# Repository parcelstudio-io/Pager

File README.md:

# Mochi Pager

Mochi Pager is a pager-sized, expressive voice AI companion. The first product target is a rounded handheld device with two large round eyes, curious idle gaze, a sliding live caption, microphone, speaker, Wi-Fi, BLE, and optional standalone 4G LTE—and exactly two physical controls: the top conversation button and a power slide switch. The conversation button deliberately opens or closes a visibly live session; while it is open, the user and assistant can speak in a full-duplex, voice-interruptible conversation without pressing for each turn, while the assistant's words slide through the caption below its face. A companion mobile app onboards the device over BLE (Wi-Fi credentials, cellular APN, account claiming) and shows an encrypted local cache of opt-in cloud conversation history. The pager connects through a private gateway to the OpenAI Realtime API; it does not run the language model on the device.

The current phase is V1 interaction implementation plus EVT (engineering validation) planning. A zero-dependency local session broker and browser device simulator now provide the first runnable full-duplex slice; embedded firmware, the mobile app, cloud history, and cellular work remain staged behind it.

## Start here

- [Product concept](docs/design/0001_mochi_pager_product_concept.md)
- [V1 prototype high-level design](docs/prototype/0001_v1_high_level_design.md)
- [V1 beginner build guide and exact materials](docs/prototype/0002_v1_beginner_build_guide.md)
- [Companion app and synchronization architecture](docs/design/0002_companion_app_and_sync_architecture.md)
- [Carrier board hardware design](docs/design/0003_mochi_carrier_board_design.md)
- [MVP requirements](docs/requirements/0001_mvp_requirements.md)
- [Component sources and staged BOM](docs/research/0001_component_sources_and_bom.md)
- [Shared-conversation and video source audit](docs/research/0002_reference_observations.md)
- [Independent verification and corrections](docs/research/0003_independent_verification_and_corrections.md)
- [35-project-day build plan plus companion-app track](scrum/20260830/task_0001/daily_plan.md)
- [Technical decision log](docs/decisions/README.md)
- [Beginner IoT and electrical-engineering course](edu/README.md)

## Current verdict

The interaction mule is already ordered: one full M5Stack CoreS3 K128, recorded in the [daily log](scrum/20260830/task_0001/daily_log.md). Confirm only a known-good data-capable USB-C cable now; do not buy a second CoreS3. First run the laptop V1-A slice, then use the K128's documented full-duplex audio path to measure simultaneous capture/playback, AEC feasibility, voice barge-in, on-device captions, and truthful session indication. Use Wi-Fi and then a phone hotspot before adding radio complexity. Buy the separate SIM7600G-H cellular mule only after the Wi-Fi full-duplex vertical slice passes its gate. Do not buy a final battery, custom display, bare cellular module, or 5G hardware yet.

This ordering protects the project from three expensive early mistakes: choosing an enclosure before measuring the parts, choosing a battery before measuring modem peaks, and integrating RF onto the first PCB.

The major load-bearing claims reviewed in the 2026-08-30/31 verification pass, its corrections, and its explicitly unverifiable items are logged in [research 0003](docs/research/0003_independent_verification_and_corrections.md). That pass also added requirements the first draft missed: the sliding caption, companion app, and two-control constraint.

## Run V1-A now

Node.js 20 or newer and an OpenAI API project are required. The standard API key stays in the local server process.

```bash
cp .env.example .env
# Edit .env and replace OPENAI_API_KEY=replace_me
npm test
npm start
```

Then open `http://localhost:3000`. No `npm install` is required because V1-A has no runtime package dependencies. The idle face begins calm and centered: its first curious gesture arrives after 3–5 seconds, later gestures follow 6–12 second pauses, and every synchronized up/down glance, side-to-side look-around, or clockwise/counterclockwise roll returns to center. Each gesture now uses brief saccades separated by still fixations instead of continuous pupil drift; the cream eye aperture follows vertical gaze like an eyelid opening, while speaking no longer produces a rhythmic eye bob. Conversation and battery state take priority. Face animation loads as an optional enhancement after Start/Stop is wired, so an animation import or initialization failure leaves a static face without disabling conversation control. The gateway renders the versioned [`prompt/mochi-realtime.ftl`](prompt/mochi-realtime.ftl) on the server, so the browser cannot inject history or system instructions. The localhost default has no real account/history service and truthfully marks that context unavailable. API use may incur charges; set a conservative project budget before testing. The [beginner build guide](docs/prototype/0002_v1_beginner_build_guide.md) contains the complete safety, setup, acceptance, and CoreS3 bring-up sequence.

## Repository organization

```text
docs/
  decisions/       numbered architecture decision records (ADRs)
  design/          product and industrial-design specifications
  requirements/    measurable product requirements
  research/        source audits, comparisons, and BOMs
edu/               progressive IoT and electrical-engineering course for software engineers
prompt/            version-controlled server-side Realtime instruction templates
scrum/
  YYYYMMDD/
    task_NNNN/      task brief, daily plan, evidence, and retrospective
hardware/           future PCB and mechanical source files
src/                production device, gateway, companion-app, and cloud code only
tests/              automated tests spanning production components
tools/              simulators, fixtures, flashing, and developer utilities
```

Create directories only when they gain real content. When implementation begins, a sensible source split is `src/device/`, `src/gateway/`, `src/app/` (the companion mobile app), and `src/cloud/`. Hardware design should live in `hardware/pcb/` and `hardware/mechanical/`, not under `src/`.

Task IDs are repository-wide, zero-padded, and monotonically increasing. Decision records have their own monotonically increasing sequence because a decision's history is independent of sprint/task history. Never renumber an accepted or superseded record.

## Reference boundary

The shared ChatGPT post exposes only one answer, which proposes a **95 × 60 × 30 mm** enclosure. The earlier conversation is not present in the public page, so this repository treats that size as a maximum envelope rather than inventing unavailable prior decisions.

The visual reference is Huy Vector's [Tiny Pocket AI Assistant](https://www.youtube.com/watch?v=25RGnr407PM) and its [build guide](https://www.huyvector.org/robots-kinetic/pocket-ai-assistant). We borrow its face-first charm, blinking eyes, compact status text, and cheeky personality. We do not copy its exposed battery, conductive frame, cloud service, or electronics as a product architecture.

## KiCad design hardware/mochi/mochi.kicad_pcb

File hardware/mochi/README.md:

# Mochi R1 Walter carrier

This directory contains a deterministic **electrical reference and placement study** for
the pager-size Mochi companion. It is intentionally useful for architecture review,
firmware pin contracts, component purchasing, and mechanical experiments. It is **not a
fabrication release**.

The current baseline is a 60 × 82 × 1.2 mm four-layer carrier around the orderable
QuickSpot Walter LTE-M/Wi-Fi/BLE/GNSS SoM. The previously proposed MIKROE-6396 Click was
removed because its official product page now reports it unavailable. The design decision
and alternatives are recorded in [ADR 0013](../../docs/decisions/0013_use_walter_family_for_rev_a_evt.md).

## Files

- [`mochi.kicad_sch`](mochi.kicad_sch) — KiCad system-level schematic.
- [`mochi.kicad_pcb`](mochi.kicad_pcb) — four-layer outline and reviewed component
  placement; intentionally unrouted.
- [`doc/design_manifest.json`](doc/design_manifest.json) — machine-readable electrical,
  configuration, and release-boundary contract.
- [`doc/bom.csv`](doc/bom.csv) — proposed parts and DNP state.
- [`doc/connectivity.csv`](doc/connectivity.csv) — exact named-net endpoints.
- [`doc/pin_map.csv`](doc/pin_map.csv) — Walter/ESP32 GPIO assignment.
- [`doc/bringup_and_validation.md`](doc/bringup_and_validation.md) — physical proof plan.
- [`doc/research_matrix.md`](doc/research_matrix.md) — dated primary-source comparison.
- [`reports/`](reports/) — KiCad/MCP and command-line check evidence.

The generated `Mochi_Reference.pretty` footprints are review geometry, except that the
Walter header pitch, pin order, pad centers, and antenna keepout follow QuickSpot's open
footprint. Every footprint must still be replaced or independently checked against the
exact ordered part and assembly process before fabrication.

## Reproduce the desk checks

From the repository root:

```bash
node tools/hardware/generate_mochi_reference.js
python3 tools/hardware/check_carrier_design.py
```

The current expected result is **66 passed, 2 warnings, 0 failed**. The warnings are
deliberate: the PCB has no routes, and the back-mounted Walter reference produces one
library-parity warning. KiCad ERC is zero. KiCad DRC otherwise reports the 168 expected
unconnected items and no unexpected physical-rule category.

KiCad MCP was also pointed at this exact project. Its full production quality gate is
expected to fail and is retained as useful evidence: a label-oriented system schematic
has zero explicit wires, the PCB is unrouted, and reference footprints are not a release
library. MCP did confirm clean ERC, 100% schematic-to-PCB named-pad transfer, matching
reference sets, a 60 × 82 mm frame, and zero courtyard issues.

## What the board connects

```text
USB-C charge only ─ protection ─ BQ25628E ─ SYS_ALWAYS ─ TPS22950 ─ SYS_SW ─ Walter VIN
                             │                    ▲                    └─ 200uF EVT reservoir
protected 1S pack + NTC ─────┘                    │
                                           latching slide

SYS_SW ─ TPS63802 ─ 3V3_PERIPH ─┬─ LCD + touch
                                ├─ MAX98357A ─ differential 8ohm speaker
                                ├─ TPS22918 ─ MIC_3V3 ─ PDM mic + isolation + cyan LED
                                └─ DNP TPS22918 ─ Arducam Mega + white LED
```

Walter contains the ESP32-S3, Wi-Fi/BLE, LTE-M/NB-IoT modem, nano-SIM, GNSS, RF front
end, and modem-to-ESP UART. The carrier therefore does not route a 50-ohm cellular trace,
SIM bus, 1.8 V modem GPIO, or user USB data.

## Stop conditions

Do not order a PCB from this directory until all of these are true:

- production symbols, footprints, land patterns, paste apertures, and exact order codes
  are frozen;
- the schematic is redrawn with conventional wires/hierarchy and peer-reviewed;
- the power stages are laid out from vendor reference layouts and the entire PCB is
  routed with zero unexplained ERC/DRC findings;
- enclosure CAD closes around the display, battery, speaker cavity, module, USB, switches,
  coax bends, and LTE antenna;
- a physical prototype passes the validation plan; and
- an RF/certification lab accepts the portable simultaneous-transmitter plan.

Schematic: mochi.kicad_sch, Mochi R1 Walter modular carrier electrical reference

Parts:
C1: 1uF 25V X7R; C1_C0603
C2: 10uF 25V X7R; C2_C0805
C3: 100nF 25V X7R; C3_C0402
C4: 47nF 25V X7R; C4_C0402
C5: 4.7uF 10V X7R; C5_C0603
C6: 10uF 10V X7R; C6_C0805
C7: 10uF 10V X7R; C7_C0805
C8: 10uF 10V X7R; C8_C0805
C9: 100nF 10V X7R; C9_C0402
C10: 1uF 10V X7R; C10_C0603
C11: 10uF 10V X7R; C11_C0805
C12: 10uF 10V X7R; C12_C0805
C13: 22uF 6.3V X7R; C13_C0805
C14: 100uF 6.3V low-ESR; C14_C1210
C15: 100uF 6.3V low-ESR; C15_C1210
C16: 10uF 10V X7R; C16_C0805
C17: 100nF 10V X7R; C17_C0402
C18: 1uF 6.3V X7R; C18_C0603
C19: 10uF 6.3V X7R; C19_C0805
C20: 100nF 6.3V X7R; C20_C0402
D1: CYAN CAPTURE LED; D1_LED0402
D2: AMBER BUTTON LED; D2_LED0402
D3: WHITE CAMERA POWER LED DNP; D3_LED0402; not fitted
D4: ESDA7P60-1U1M; D4_QFN-2
F1: 1206L075/24; F1_F1206
J1: USB4105-GF-A; J1_USB-C-16P
J2: Molex 5023520300; J2_DuraClik-3P-RA
J4: AS01808AO-SC18-WP-R; J4_Speaker-18x13-Spring
J5: WAVESHARE 1.69IN TOUCH LCD 27057; J5_GH1.25-12P-RA-VERIFY
J6: ARDUCAM MEGA 3MP B0400 DNP; J6_XH2.54-1x6-RA; not fitted
L1: 1uH XGL4020-102; L1_L4x4
L2: 0.47uH XFL4015-471; L2_L4x4
MK1: IM69D129F; MK1_MEMS-5-3.5x2.65-BOTTOM-PORT
R1: 5.1k 1%; R1_R0402
R2: 5.1k 1%; R2_R0402
R3: 4.99k 1%; R3_R0402
R4: 5.23k 1%; R4_R0402
R5: 30.1k 1%; R5_R0402
R6: 100k 1%; R6_R0402
R7: 523R 1%; R7_R0402
R8: 511k 1%; R8_R0402
R9: 91k 1%; R9_R0402
R10: 4.7k 1%; R10_R0402
R11: 4.7k 1%; R11_R0402
R12: 10k 1%; R12_R0402
R13: 1.5k 1%; R13_R0402
R14: 100k 1%; R14_R0402
R15: 1.5k 1%; R15_R0402
R16: 100k 1%; R16_R0402
R17: 100k 1% DNP; R17_R0402; not fitted
R18: 1.5k 1% DNP; R18_R0402; not fitted
RS1: 10m 1% Kelvin; RS1_R1206-Kelvin
SW1: LATCHING POWER SLIDE; SW1_Slide-SPST-RA-TBD
SW2: ILLUMINATED CONVERSATION BUTTON; SW2_Top-Button-TBD
TP1: DEBUG_TX; TP1_TestPoint-1mm
TP2: DEBUG_RX; TP2_TestPoint-1mm
TP3: WALTER_DFU_N; TP3_TestPoint-1mm
TP4: WALTER_RESET_N; TP4_TestPoint-1mm
TP5: MAIN_FAULT_N; TP5_TestPoint-1mm
TP6: 3V3_POWER_GOOD; TP6_TestPoint-1mm
TP7: BQ_INTERRUPT; TP7_TestPoint-1mm
TP8: GROUND; TP8_TestPoint-1mm
TP9: WALTER_3V3_OUT; TP9_TestPoint-1mm
TP10: GAUGE_ALERT; TP10_TestPoint-1mm
TP11: BQ_POWER_GOOD; TP11_TestPoint-1mm
U1: TPD2EUSB30; U1_SOT23-3
U3: BQ25628E; U3_WQFN-18-2.5x3
U4: MAX17055ETB+T; U4_TDFN-10-2x2.5
U5: TPS22950; U5_SOT23-6
U6: TPS63802; U6_VSON-10-3x2
U10: WALTER P000000100 N16R2; U10_WALTER-28-REF
U12: TPS22918; U12_SOT23-6
U13: SN74LVC2G125; U13_VSSOP-8
U14: MAX98357AETE+T; U14_TQFN-16-3x3
U15: TPS22918 DNP CAMERA; U15_SOT23-6; not fitted

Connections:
3V3_PERIPH: C13.1, C19.1, C20.1, J5.1 (VCC), R8.1, R10.2, R11.2, R12.2, U6.5 (VOUT), U12.1 (VIN), U14.1 (VDD), U15.1 (VIN)
3V3_PG_TP: TP6.1, U6.7 (PG)
AMBER_LED: D2.1 (A), U10.13 (IO2)
AMBER_LED_K: D2.2 (K), R13.1
AMP_SD: R16.1, U10.12 (IO42), U14.6 (SD_MODE)
BAT_NTC: J2.2 (NTC), R4.2, R5.1, U3.11 (TS)
BB_FB: R8.2, R9.1, U6.6 (FB)
BB_L1: L2.1, U6.3 (L1)
BB_L2: L2.2, U6.4 (L2)
BQ_BTST: C4.1, U3.4 (BTST)
BQ_INT_N_TP: TP7.1, U3.14 (INT_N)
BQ_PG_N_TP: TP11.1, U3.15 (PG_N)
BQ_PMID: C2.1, C3.1, U3.2 (PMID)
BQ_REGN: C5.1, U3.5 (REGN)
BQ_SW: C4.2, L1.1, U3.3 (SW)
BTN_CONV: R12.1, SW2.1 (SIGNAL), U10.10 (IO40)
CAM_3V3: D3.1 (A), J6.1 (VCC), U15.3 (VOUT)
CAM_CS: J6.6 (CS), U10.14 (IO1)
CAM_EN: R17.1, U10.21 (IO17), U15.2 (EN)
CAM_LED_K: D3.2 (K), R18.1
CAPTURE_EN: R14.1, U10.11 (IO41), U12.2 (EN)
CYAN_LED_K: D1.2 (K), R15.1
DBG_RX: TP2.1, U10.2 (IO44/RX0)
DBG_TX: TP1.1, U10.3 (IO43/TX0)
GAUGE_ALRT_N: TP10.1, U4.6 (ALRT_N)
GND: C1.2, C2.2, C3.2, C5.2, C6.2, C7.2, C8.2, C9.2, C10.2, C11.2, C12.2, C13.2, C14.2, C15.2, C16.2, C17.2, C18.2, C19.2, C20.2, D4.2 (A), J1.2 (GND), J1.5 (SHIELD), J5.2 (GND), J6.2 (GND), MK1.2 (GND), MK1.5 (L/R), R1.2, R2.2, R3.2, R5.2, R6.2, R7.2, R9.2, R13.2, R14.2, R15.2, R16.2, R17.2, R18.2, RS1.2 (SYSTEM), SW2.2 (GND), TP8.1, U1.3 (GND), U3.8 (GND), U3.16 (CE_N), U4.3 (CSN), U5.6 (GND), U6.8 (GND), U10.27 (GND), U12.4 (GND), U13.2 (GND), U13.3 (OE1_N), U13.6 (OE2_N), U14.2 (GND), U15.4 (GND)
I2C_SCL: J5.10 (TP_SCL), R11.1, U3.13 (SCL), U4.5 (SCL), U10.24 (IO9)
I2C_SDA: J5.9 (TP_SDA), R10.1, U3.12 (SDA), U4.4 (SDA), U10.23 (IO8)
I2S_BCLK: U10.17 (IO6), U14.3 (BCLK)
I2S_DOUT: U10.19 (IO15), U14.5 (DIN)
I2S_LRCLK: U10.18 (IO7), U14.4 (LRCLK)
LCD_BL: J5.8 (LCD_BL), U10.9 (IO39)
LCD_CS: J5.5 (LCD_CS), U10.25 (IO10)
LCD_DC: J5.6 (LCD_DC), U10.8 (IO38)
MAIN_FLT_N: TP5.1, U5.5 (FLT_N)
MAIN_ILIM: R7.1, U5.4 (ILIM)
MIC_3V3: C18.1, D1.1 (A), MK1.1 (VDD), U12.3 (VOUT), U13.1 (VCC)
PACK_N: J2.3 (PACK-), RS1.1 (PACK), U4.2 (CSP)
PACK_P: C8.1, C9.1, J2.1 (PACK+), U3.6 (BAT), U4.1 (BATT)
PDM_CLK_MCU: U10.15 (IO4), U13.4 (A1)
PDM_CLK_MIC: MK1.3 (CLK), U13.5 (Y1)
PDM_DATA_MCU: U10.16 (IO5), U13.8 (Y2)
PDM_DATA_MIC: MK1.4 (DATA), U13.7 (A2)
PWR_SW_ON: R6.1, SW1.2 (ON), U5.2 (ON)
SPI_MISO: J6.4 (MISO), U10.7 (IO13)
SPI_MOSI: J5.3 (LCD_DIN), J6.5 (MOSI), U10.6 (IO11)
SPI_SCK: J5.4 (LCD_CLK), J6.3 (SCK), U10.5 (IO12)
SPK_N: J4.2 (-), U14.8 (OUTN)
SPK_P: J4.1 (+), U14.7 (OUTP)
SYS_ALWAYS: C6.1, C7.1, C10.1, L1.2, SW1.1 (COMMON), U3.7 (SYS), U5.1 (VIN)
SYS_SW: C11.1, C12.1, C14.1, C15.1, C16.1, C17.1, U5.3 (VOUT), U6.1 (VIN), U6.2 (EN), U10.28 (VIN)
TOUCH_IRQ: J5.12 (TP_IRQ), U10.20 (IO16)
TS_BIAS: R4.1, U3.10 (TS_BIAS)
UI_RST_N: J5.7 (LCD_RST), J5.11 (TP_RST), U10.22 (IO18)
USB_CC1: J1.3 (CC1), R1.1, U1.1 (IO1)
USB_CC2: J1.4 (CC2), R2.1, U1.2 (IO2)
USB_ILIM_500MA: R3.1, U3.9 (ILIM)
VBUS_5V: C1.1, F1.2, U3.1 (VBUS)
VBUS_CONN: D4.1 (K), F1.1, J1.1 (VBUS)
WALTER_3V3_TP: TP9.1, U10.26 (3V3_OUT)
WALTER_DFU_N: TP3.1, U10.4 (IO0/DFU/3V3_EN)
WALTER_RESET_N: TP4.1, U10.1 (RESET/EN)

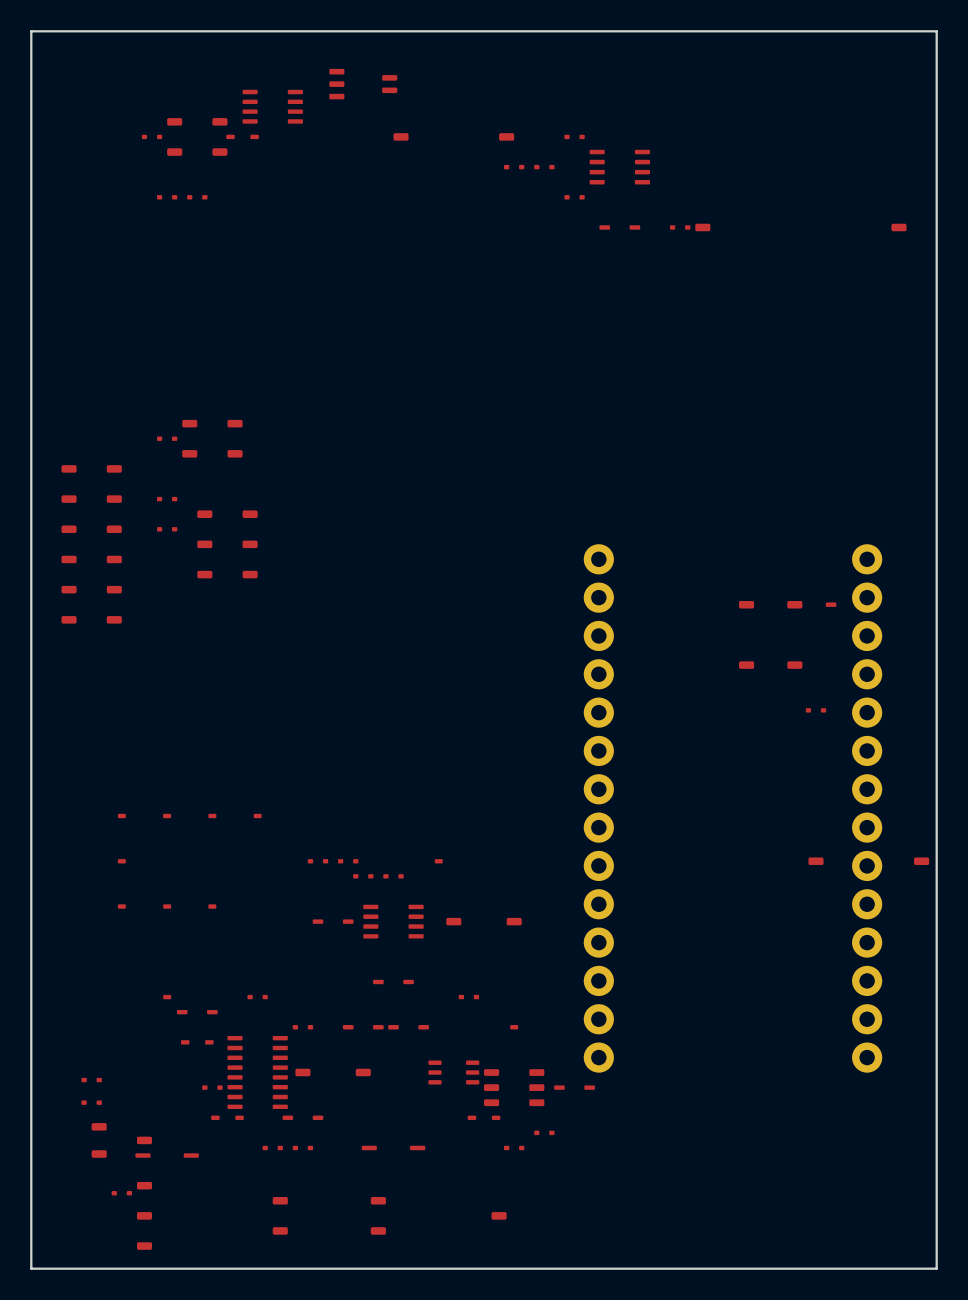
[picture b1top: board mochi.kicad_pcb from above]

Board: 4 copper layers, 60.0 x 82.0 mm, 75 parts (1 on the bottom side), 62 nets, no tracks yet.

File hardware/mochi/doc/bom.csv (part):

reference,value_or_mpn,manufacturer,role,population,datasheet,footprint_status
J1,USB4105-GF-A,GCT,User USB-C charge-only receptacle,FIT,https://gct.co/connector/usb4105,REFERENCE_ONLY_VERIFY_BEFORE_FAB
U1,TPD2EUSB30,Texas Instruments,USB-C CC1/CC2 ESD protection,FIT,https://www.ti.com/product/TPD2EUSB30,REFERENCE_ONLY_VERIFY_BEFORE_FAB
D4,ESDA7P60-1U1M,STMicroelectronics,USB VBUS TVS,FIT,https://www.st.com/en/protections-and-emi-filters/esda7p60-1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,REFERENCE_ONLY_VERIFY_BEFORE_FAB
F1,1206L075/24,Littelfuse,Resettable USB input fuse,FIT,https://www.littelfuse.com/products/polyswitch-resettable-pp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,REFERENCE_ONLY_VERIFY_BEFORE_FAB
R1,5.1k 1%,Generic,USB-C CC1 Rd,FIT,,REFERENCE_ONLY_VERIFY_BEFORE_FAB
R2,5.1k 1%,Generic,USB-C CC2 Rd,FIT,,REFERENCE_ONLY_VERIFY_BEFORE_FAB
U3,BQ25628E,Texas Instruments,1-cell 2A NVDC charger and power path,FIT,https://www.ti.com/lit/ds/symlink/bq25628e.pdf,REFERENCE_ONLY_VERIFY_BEFORE_FAB
L1,1uH XGL4020-102,Coilcraft,BQ25628E power-path inductor,FIT,https://www.coilcraft.com/en-us/products/power/shielded-indu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,REFERENCE_ONLY_VERIFY_BEFORE_FAB
C1,1uF 25V X7R,Generic,BQ VBUS bypass,FIT,,REFERENCE_ONLY_VERIFY_BEFORE_FAB
C2,10uF 25V X7R,Generic,BQ PMID bulk,FIT,,REFERENCE_ONLY_VERIFY_BEFORE_FAB
C3,100nF 25V X7R,Generic,BQ PMID high-frequency bypass,FIT,,REFERENCE_ONLY_VERIFY_BEFORE_FAB
C4,47nF 25V X7R,Generic,BQ bootstrap capacitor,FIT,,REFERENCE_ONLY_VERIFY_BEFORE_FAB
C5,4.7uF 10V X7R,Generic,BQ REGN bypass,FIT,,REFERENCE_ONLY_VERIFY_BEFORE_FAB
C6,10uF 10V X7R,Generic,BQ SYS bulk 1 of 2,FIT,,REFERENCE_ONLY_VERIFY_BEFORE_FAB
C7,10uF 10V X7R,Generic,BQ SYS bulk 2 of 2,FIT,,REFERENCE_ONLY_VERIFY_BEFORE_FAB
C8,10uF 10V X7R,Generic,BQ BAT bypass,FIT,,REFERENCE_ONLY_VERIFY_BEFORE_FAB
R3,4.99k 1%,Generic,"BQ input-current limit, about 500mA",FIT,https://www.ti.com/lit/ds/symlink/bq25628e.pdf,REFERENCE_ONLY_VERIFY_BEFORE_FAB
R4,5.23k 1%,Generic,BQ TS upper resistor for 103AT-class NTC,FIT,https://www.ti.com/lit/ds/symlink/bq25628e.pdf,REFERENCE_ONLY_VERIFY_BEFORE_FAB
R5,30.1k 1%,Generic,BQ TS lower resistor for 103AT-class NTC,FIT,https://www.ti.com/lit/ds/symlink/bq25628e.pdf,REFERENCE_ONLY_VERIFY_BEFORE_FAB
J2,Molex 5023520300,Molex,Protected pack connector,FIT,https://www.molex.com/en-us/products/part-detail/5023520300,REFERENCE_ONLY_VERIFY_BEFORE_FAB
RS1,10m 1% Kelvin,Vishay or equivalent,Fuel-gauge low-side shunt,FIT,,REFERENCE_ONLY_VERIFY_BEFORE_FAB
U4,MAX17055ETB+T,Analog Devices,Fuel gauge with current and time estimation,FIT,https://www.analog.com/en/products/MAX17055.html,REFERENCE_ONLY_VERIFY_BEFORE_FAB
C9,100nF 10V X7R,Generic,Fuel-gauge bypass,FIT,,REFERENCE_ONLY_VERIFY_BEFORE_FAB
SW1,LATCHING POWER SLIDE,C&K or Alps TBD,Only latching hardware power control,FIT,,REFERENCE_ONLY_VERIFY_BEFORE_FAB
R6,100k 1%,Generic,Power-enable fail-safe pull-down,FIT,,REFERENCE_ONLY_VERIFY_BEFORE_FAB
U5,TPS22950,Texas Instruments,Reverse-blocking adjustable-current-limit master load switch,FIT,https://www.ti.com/lit/ds/symlink/tps22950.pdf,REFERENCE_ONLY_VERIFY_BEFORE_FAB
R7,523R 1%,Generic,TPS22950 nominal about 2.4A current limit,FIT,https://www.ti.com/lit/ds/symlink/tps22950.pdf,REFERENCE_ONLY_VERIFY_BEFORE_FAB
C10,1uF 10V X7R,Generic,Master-switch input bypass,FIT,,REFERENCE_ONLY_VERIFY_BEFORE_FAB
C11,10uF 10V X7R,Generic,Master-switch output bulk,FIT,,REFERENCE_ONLY_VERIFY_BEFORE_FAB
U6,TPS63802,Texas Instruments,2A 3.3V peripheral buck-boost,FIT,https://www.ti.com/lit/ds/symlink/tps63802.pdf,REFERENCE_ONLY_VERIFY_BEFORE_FAB
L2,0.47uH XFL4015-471,Coilcraft,TPS63802 buck-boost inductor,FIT,https://www.coilcraft.com/en-us/products/power/shielded-indu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,REFERENCE_ONLY_VERIFY_BEFORE_FAB
R8,511k 1%,Generic,TPS63802 3.3V feedback upper,FIT,,REFERENCE_ONLY_VERIFY_BEFORE_FAB
R9,91k 1%,Generic,TPS63802 3.3V feedback lower,FIT,,REFERENCE_ONLY_VERIFY_BEFORE_FAB
C12,10uF 10V X7R,Generic,TPS63802 input bulk,FIT,,REFERENCE_ONLY_VERIFY_BEFORE_FAB
C13,22uF 6.3V X7R,Generic,TPS63802 output bulk,FIT,,REFERENCE_ONLY_VERIFY_BEFORE_FAB
R10,4.7k 1%,Generic,I2C SDA pull-up,FIT,,REFERENCE_ONLY_VERIFY_BEFORE_FAB
R11,4.7k 1%,Generic,I2C SCL pull-up,FIT,,REFERENCE_ONLY_VERIFY_BEFORE_FAB
U10,WALTER P000000100 N16R2,QuickSpot/DPTechnics,ESP32-S3 Wi-Fi/BLE plus Sequans GM02SP LTE-M/NB-IoT/GNSS SoM,FIT,https://quickspot.io/datasheet/walter_datasheet.pdf,REFERENCE_ONLY_VERIFY_BEFORE_FAB
C14,100uF 6.3V low-ESR,Panasonic or equivalent,Walter VIN EVT reservoir 1 of 2,FIT,,REFERENCE_ONLY_VERIFY_BEFORE_FAB
C15,100uF 6.3V low-ESR,Panasonic or equivalent,Walter VIN EVT reservoir 2 of 2,FIT,,REFERENCE_ONLY_VERIFY_BEFORE_FAB
C16,10uF 10V X7R,Generic,Walter VIN local bypass,FIT,,REFERENCE_ONLY_VERIFY_BEFORE_FAB
C17,100nF 10V X7R,Generic,Walter VIN high-frequency bypass,FIT,,REFERENCE_ONLY_VERIFY_BEFORE_FAB
SW2,ILLUMINATED CONVERSATION BUTTON,TBD,Only momentary user control; amber LED is D2,FIT,,REFERENCE_ONLY_VERIFY_BEFORE_FAB
R12,10k 1%,Generic,Conversation-button pull-up,FIT,,REFERENCE_ONLY_VERIFY_BEFORE_FAB
D2,AMBER BUTTON LED,TBD,Connecting and session-intent indicator inside SW2,FIT,,REFERENCE_ONLY_VERIFY_BEFORE_FAB
R13,1.5k 1%,Generic,Amber LED current limit,FIT,,REFERENCE_ONLY_VERIFY_BEFORE_FAB
U12,TPS22918,Texas Instruments,Hardware microphone rail gate,FIT,https://www.ti.com/lit/ds/symlink/tps22918.pdf,REFERENCE_ONLY_VERIFY_BEFORE_FAB
R14,100k 1%,Generic,Capture-enable fail-safe pull-down,FIT,,REFERENCE_ONLY_VERIFY_BEFORE_FAB
C18,1uF 6.3V X7R,Generic,Switched microphone-rail bypass,FIT,,REFERENCE_ONLY_VERIFY_BEFORE_FAB
U13,SN74LVC2G125,Texas Instruments,PDM clock and data isolation with Ioff,FIT,https://www.ti.com/lit/ds/symlink/sn74lvc2g125.pdf,REFERENCE_ONLY_VERIFY_BEFORE_FAB
MK1,IM69D129F,Infineon,Bottom-port PDM microphone,FIT,https://www.infineon.com/part/IM69D129F,REFERENCE_ONLY_VERIFY_BEFORE_FAB
D1,CYAN CAPTURE LED,TBD,Hardware-coupled capture truth indicator,FIT,,REFERENCE_ONLY_VERIFY_BEFORE_FAB
R15,1.5k 1%,Generic,Cyan LED current limit,FIT,,REFERENCE_ONLY_VERIFY_BEFORE_FAB
U14,MAX98357AETE+T,Analog Devices,I2S mono class-D amplifier,FIT,https://www.analog.com/en/products/max98357a.html,REFERENCE_ONLY_VERIFY_BEFORE_FAB
R16,100k 1%,Generic,Amplifier shutdown pull-down,FIT,,REFERENCE_ONLY_VERIFY_BEFORE_FAB
C19,10uF 6.3V X7R,Generic,Amplifier local bulk,FIT,,REFERENCE_ONLY_VERIFY_BEFORE_FAB
C20,100nF 6.3V X7R,Generic,Amplifier high-frequency bypass,FIT,,REFERENCE_ONLY_VERIFY_BEFORE_FAB
J4,AS01808AO-SC18-WP-R,PUI Audio,8ohm 1W spring-contact speaker,FIT,https://puiaudio.com/file/specs-AS01808AO-SC18-WP-R.pdf,REFERENCE_ONLY_VERIFY_BEFORE_FAB
J5,WAVESHARE 1.69IN TOUCH LCD 27057,Waveshare,GH1.25 12-pin 240x280 ST7789V2 LCD and CST816S touch module,FIT,https://www.waveshare.com/wiki/1.69inch_Touch_LCD_Module,REFERENCE_ONLY_VERIFY_BEFORE_FAB
U15,TPS22918 DNP CAMERA,Texas Instruments,Optional camera rail gate,DNP,https://www.ti.com/lit/ds/symlink/tps22918.pdf,REFERENCE_ONLY_VERIFY_BEFORE_FAB
R17,100k 1% DNP,Generic,Camera-enable fail-safe pull-down,DNP,,REFERENCE_ONLY_VERIFY_BEFORE_FAB
J6,ARDUCAM MEGA 3MP B0400 DNP,Arducam,Six-wire SPI still-camera experiment; too large for baseline enclosure,DNP,https://docs.arducam.com/Arduino-SPI-camera/MEGA-SPI/MEGA-SP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,REFERENCE_ONLY_VERIFY_BEFORE_FAB
D3,WHITE CAMERA POWER LED DNP,TBD,Hardware-coupled camera-power indicator,DNP,,REFERENCE_ONLY_VERIFY_BEFORE_FAB
R18,1.5k 1% DNP,Generic,Camera indicator current limit,DNP,,REFERENCE_ONLY_VERIFY_BEFORE_FAB
TP1,DEBUG_TX,Generic,Factory UART TX pad; never supply power,FIT,,REFERENCE_ONLY_VERIFY_BEFORE_FAB
TP2,DEBUG_RX,Generic,Factory UART RX pad; verify no off-state injection,FIT,,REFERENCE_ONLY_VERIFY_BEFORE_FAB
TP3,WALTER_DFU_N,Generic,Factory boot and DFU pad,FIT,,REFERENCE_ONLY_VERIFY_BEFORE_FAB
TP4,WALTER_RESET_N,Generic,Factory reset pad,FIT,,REFERENCE_ONLY_VERIFY_BEFORE_FAB
TP5,MAIN_FAULT_N,Generic,Master-switch fault pad,FIT,,REFERENCE_ONLY_VERIFY_BEFORE_FAB
TP6,3V3_POWER_GOOD,Generic,Peripheral-rail validation pad,FIT,,REFERENCE_ONLY_VERIFY_BEFORE_FAB
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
